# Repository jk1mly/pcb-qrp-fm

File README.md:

# pcb-qrp-fm
おもちゃのトランシーバ用のICを使うための基板

ハムフェア2023でPRUGブースに置いたもの
フィルタ（特に145M）は改善の余地あり

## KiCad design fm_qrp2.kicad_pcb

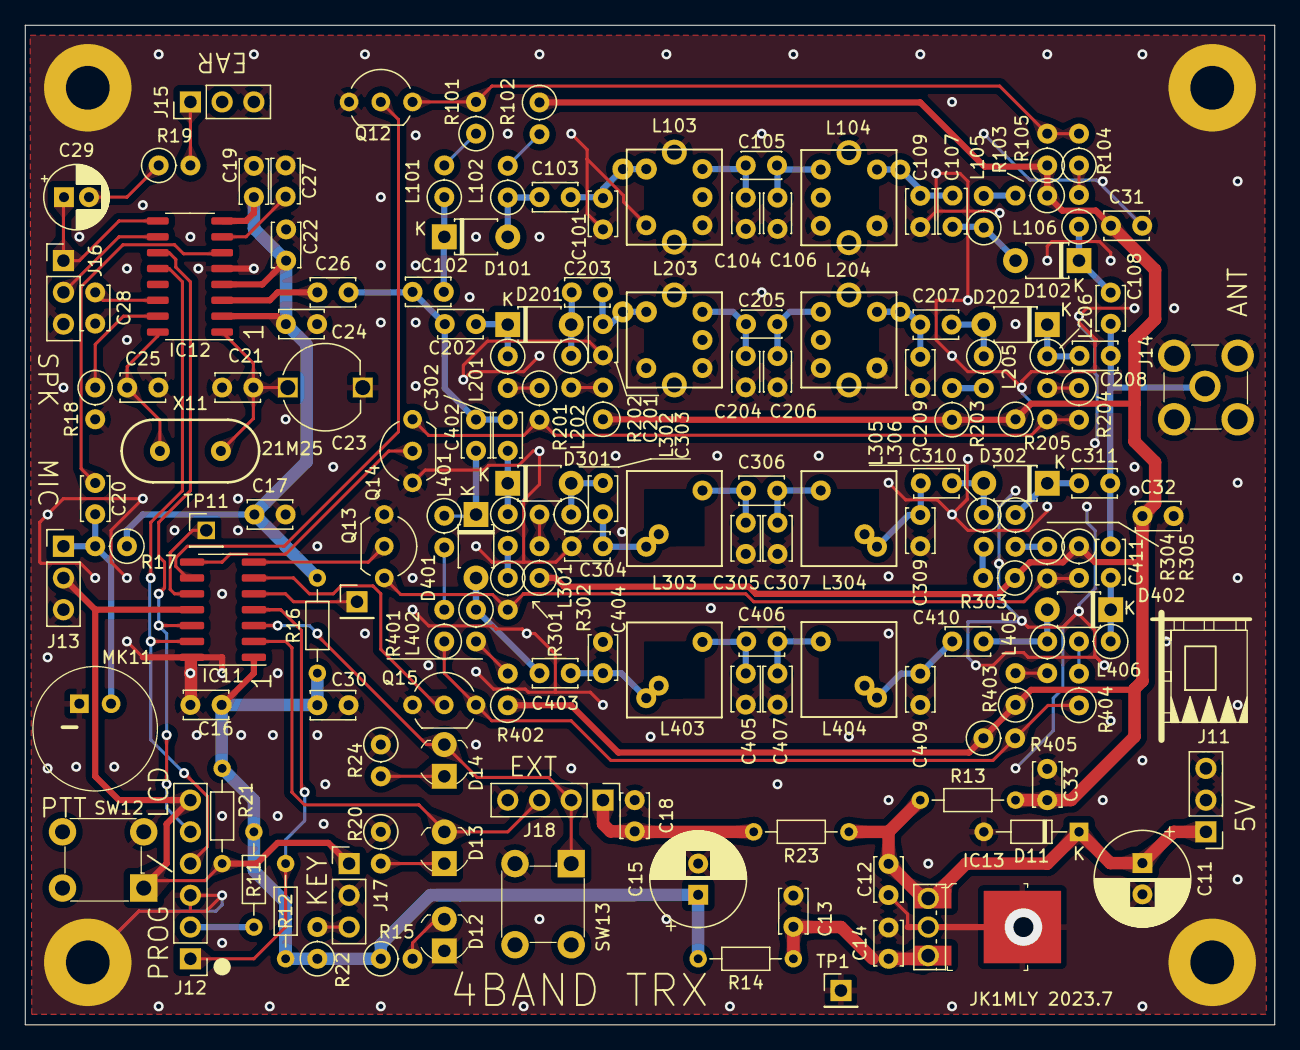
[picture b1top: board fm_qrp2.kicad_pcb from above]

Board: 2 copper layers, 100.0 x 80.0 mm, 156 parts (0 on the bottom side), 90 nets.

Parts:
C11, C15: 470u; CP_Radial_D7.5mm_P2.50mm
C12, C13, C14, C16, C18, C20, C30, C31, C32: 0.1u; C_Disc_D3.4mm_W2.1mm_P2.50mm
C17, C19, C22, C24, C27, C28, C33: 1u; C_Disc_D3.4mm_W2.1mm_P2.50mm
C21, C407: 22p; C_Disc_D3.4mm_W2.1mm_P2.50mm
C23: 10p; C_TRIM_P6.00mm
C25: 27p; C_Disc_D3.4mm_W2.1mm_P2.50mm
C26: 0.01u; C_Disc_D3.4mm_W2.1mm_P2.50mm
C29: 10u; CP_Radial_D5.0mm_P2.00mm
C101, C109, C201, C209, C405: NM; C_Disc_D3.4mm_W2.1mm_P2.50mm
C102, C108: 4700p; C_Disc_D3.4mm_W2.1mm_P2.50mm
C103, C107, C202, C203, C207, C208: 2200p; C_Disc_D3.4mm_W2.1mm_P2.50mm
C104, C106: 33p; C_Disc_D3.0mm_W2.0mm_P2.50mm
C105: 6p; C_Disc_D3.0mm_W2.0mm_P2.50mm
C204, C206: 15p; C_Disc_D3.0mm_W2.0mm_P2.50mm
C205: 2p; C_Disc_D3.0mm_W2.0mm_P2.50mm
C302, C303, C310, C311, C402, C403, C410, C411: 1000p; C_Disc_D3.4mm_W2.1mm_P2.50mm
C304, C305, C307, C309: 15p; C_Disc_D3.4mm_W2.1mm_P2.50mm
C306: 33p; C_Disc_D3.4mm_W2.1mm_P2.50mm
C404, C409: 10p; C_Disc_D3.4mm_W2.1mm_P2.50mm
C406: 4p; C_Disc_D3.4mm_W2.1mm_P2.50mm
D11: 1N4007; D_DO-34_SOD68_P7.62mm_Horizontal
D12, D13, D14: LED; LED_3mm_Radial
D101, D102, D201, D202, D301, D302, D401, D402: 1SS277; D_T-1_P5.08mm_Horizontal
IC11: PIC16F1503T-I/SL; SO-14_3.9x8.65mm_P1.27mm
IC12: BK4802P; SO-16_3.9x9.9mm_P1.27mm
IC13: LM2940T-3.3; TO-251-3_Vertical
J11, J13, J15, J16, J17: Conn_01x03; PinHeader_1x03_P2.54mm_Vertical
J12: Conn_01x06; PinHeader_1x06_P2.54mm_Vertical
J14: Conn_Coaxial; RF_SMA_Vertical_5-1814832-1
J18: Conn_01x04; PinHeader_1x04_P2.54mm_Vertical
L101, L102, L105, L106, L201, L202, L205, L206, L301, L302, L305, L306, L401, L402, L405, L406: 1u; R_Axial_DIN0207_L6.3mm_D2.5mm_P2.54mm_Vertical
L103, L104: 7S25; coil_7mm
L203, L204: 7S50; coil_7mm
L303, L304, L403, L404: 50n; coil3_7mm
MK11: Microphone; Mic_CMA-4544PF-W
Q12, Q13, Q14, Q15: 2N7000; TO-92_Inline_Wide
R11, R13, R14, R16: 0; R_Axial_DIN0204_L3.6mm_D1.6mm_P7.62mm_Horizontal
R12: 1k; R_Axial_DIN0204_L3.6mm_D1.6mm_P7.62mm_Horizontal
R15, R17, R20, R24, R101, R102, R103, R104, R105, R201, R202, R203, R204, R205, R301, R302, R303, R304, R305, R401, R402, R403, R404, R405: 1k; R_Axial_DIN0207_L6.3mm_D2.5mm_P2.54mm_Vertical
R18: 4.7k; R_Axial_DIN0207_L6.3mm_D2.5mm_P2.54mm_Vertical
R19, R22: 10; R_Axial_DIN0207_L6.3mm_D2.5mm_P2.54mm_Vertical
R21: 10k; R_Axial_DIN0204_L3.6mm_D1.6mm_P7.62mm_Horizontal
R23: 10; R_Axial_DIN0204_L3.6mm_D1.6mm_P7.62mm_Horizontal
SW12, SW13: SW_Push; Switch_Tactile_THT_6x6mm
TP1, TP11, TP12: TestPoint; PinHeader_1x01_P2.54mm_Vertical
TP2, TP3, TP4, TP5: M3; MountingHole_3.5mm_Pad
U12: NJM2391DL1-33; TO-252-3
X11: 21.25M; HC49

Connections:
+3V3: C15.1, C16.2, C30.1, IC11.1 (VDD), R11.2, R12.1, R14.2, R15.1, R16.1, R21.1, R22.1
+5V: C31.1, C32.1, C33.1, R13.2, R102.1, R103.1, R105.1, R202.1, R203.1, R205.1, R302.1, R303.1, R305.1, R402.1, R403.1, R405.1
/RF-IC/+3.3V-REG: C13.1, C14.1, IC13.3 (VO), R14.1, U12.3 (VO)
/RF-IC/+3.3V-TR: C17.1, C19.2, C22.2, C24.2, IC12.2 (VCCRF), IC12.4 (VCCPA), IC12.8 (VCCAUD), R16.2, R17.1
/RF-IC/+5VIN: C11.1, C12.1, D11.1 (K), IC13.1 (VI), J11.1, R13.1, R23.1, U12.1 (VI)
B28: Q12.3 (D), R101.2, R104.2, R105.2
B50: Q14.3 (D), R201.2, R204.2, R205.2
B144: Q13.3 (D), R301.2, R304.2, R305.2
B430: Q15.3 (D), R401.1, R404.1, R405.2
GND: C11.2, C12.2, C13.2, C14.2, C15.2, C16.1, C17.2, C18.2, C19.1, C21.2, C22.1, C23.2, C24.1, C25.2, C27.2, C28.2, C30.2, C31.2, C32.2, C33.2, C101.2, C104.2, C106.2, C109.2, C201.2, C204.2, C206.2, C209.2, C304.2, C305.2, C307.1, C309.2, C404.2, C405.2, C407.1, C409.2, D11.2 (A), D12.1 (K), IC11.14 (VSS), IC12.5 (VSS), IC13.2 (GND), J11.2, J11.3, J12.3, J13.3, J14.1 (G), J15.3, J16.3, J17.2, J18.4, L103.1 (PR1), L103.5 (S2), L103.6 (G1), L103.7 (G2), L104.3 (PR2), L104.4 (S1), L104.6 (G1), L104.7 (G2), L203.1 (PR1), L203.5 (S2), L203.6 (G1), L203.7 (G2), L204.3 (PR2), L204.4 (S1), L204.6 (G1), L204.7 (G2), MK11.1 (-), Q12.1 (S), Q13.1 (S), Q14.1 (S), Q15.1 (S), R18.2, R20.1, R24.1, SW12.2, SW13.2, TP1.1, TP2.1, TP3.1, TP4.1, TP5.1, U12.2 (GND)
unnamed: C29.2, R19.1
unnamed: C303.2, C304.1, L303.1
unnamed: C305.1, C306.1, L303.2
unnamed: C306.2, C307.2, L304.1
unnamed: C309.1, C310.1, L304.2
unnamed: C403.2, C404.1, L403.1
unnamed: C405.1, C406.1, L403.2
unnamed: C406.2, C407.2, L404.1
unnamed: C409.1, C410.1, L404.2
unnamed: D12.2 (A), R15.2
unnamed: D13.2 (A), IC11.2 (RA5/T1CKI/NCO1CLK/CLCIN1/CLKIN), J18.3
unnamed: D13.1 (K), R20.2
unnamed: D14.2 (A), IC11.3 (RA4/AN3/T1G/NCO1/SDO/CLKOUT), J18.2, SW13.1
unnamed: D14.1 (K), R24.2
unnamed: C103.1, D101.2 (A), L102.1
unnamed: C102.2, D101.1 (K), L101.1
unnamed: C107.2, D102.2 (A), L105.1
unnamed: C108.1, D102.1 (K), L106.1
unnamed: C203.1, D201.2 (A), L202.1
unnamed: C202.2, D201.1 (K), L201.1
unnamed: C207.2, D202.2 (A), L205.1
unnamed: C208.1, D202.1 (K), L206.1
unnamed: C303.1, D301.2 (A), L302.1
unnamed: C302.2, D301.1 (K), L301.1
unnamed: C310.2, D302.2 (A), L305.1
unnamed: C311.1, D302.1 (K), L306.1
unnamed: C403.1, D401.2 (A), L402.1
unnamed: C402.2, D401.1 (K), L401.1
unnamed: C410.2, D402.2 (A), L405.1
unnamed: C411.1, D402.1 (K), L406.1
unnamed: IC11.6 (CLC2IN1/CWG1B/C2OUT/RC4), Q15.2 (G)
unnamed: IC11.5 (PWM1/CLC1/CWG1A/RC5), TP12.1
unnamed: IC11.13 (RA0/AN0/DACOUT1/C1IN+/ICSPDAT), IC12.12 (SDATA), J12.4
unnamed: IC11.12 (RA1/AN1/Vref+/C1IN0-/C2IN0-/ICSPCLK), IC12.11 (SCK), J12.5
unnamed: IC11.11 (RA2/AN2/DACOUT2/C1OUT/T0CKI/~CWG1FLT/CL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), J12.6, J13.2, J17.1, R21.2, SW12.1
unnamed: IC11.4 (RA3/T1G/CLC1IN0/~SS/~MCLR/Vpp), J12.1, R12.2
unnamed: IC11.10 (SCK/SCL/CLC2/C2IN+/AN4/RC0), TP11.1
unnamed: IC11.9 (SDI/SDA/PWM4/NCO1/C2IN1-/C1IN1-/AN5/RC1), Q12.2 (G)
unnamed: IC11.8 (SDO/C2IN2-/C1IN2-/AN6/RC2), Q14.2 (G)
unnamed: IC11.7 (~SS/PWM2/CLCIN0/C2IN3-/C1IN3-/AN7/RC3), Q13.2 (G)
unnamed: C26.1, IC12.3 (ANT)
unnamed: C27.1, IC12.7 (AUDC)
unnamed: C28.1, IC12.14 (CDVDD)
unnamed: IC12.10 (EARON), J16.2
unnamed: C29.1, IC12.9 (EAROP), J16.1
unnamed: C20.2, IC12.6 (MIC)
unnamed: IC12.15 (SQ), R18.1
unnamed: C21.1, C23.1, IC12.1 (XI), X11.1
unnamed: C25.1, IC12.16 (XO), X11.2
unnamed: J12.2, R11.1
unnamed: C20.1, J13.1, MK11.2 (+), R17.2
unnamed: J15.1, R19.2
unnamed: J17.3, R22.2
unnamed: C18.1, J18.1, R23.2
unnamed: L101.2, R101.1
unnamed: L102.2, R102.2
unnamed: C104.1, C105.2, L103.3 (PR2)
unnamed: C101.1, C103.2, L103.4 (S1)
unnamed: C105.1, C106.1, L104.1 (PR1)
unnamed: C107.1, C109.1, L104.5 (S2)
unnamed: L105.2, R103.2
unnamed: L106.2, R104.1
unnamed: L201.2, R201.1
unnamed: L202.2, R202.2
unnamed: C204.1, C205.2, L203.3 (PR2)
unnamed: C201.1, C203.2, L203.4 (S1)
unnamed: C205.1, C206.1, L204.1 (PR1)
unnamed: C207.1, C209.1, L204.5 (S2)
unnamed: L205.2, R203.2
unnamed: L206.2, R204.1
unnamed: L301.2, R301.1
unnamed: L302.2, R302.2
unnamed: L305.2, R303.2
unnamed: L306.2, R304.1
unnamed: L401.2, R401.2
unnamed: L402.2, R402.2
unnamed: L405.2, R403.2
unnamed: L406.2, R404.2
RFANT: C108.2, C208.2, C311.2, C411.2, J14.2 (S)
RFIO: C26.2, C102.1, C202.1, C302.1, C402.1

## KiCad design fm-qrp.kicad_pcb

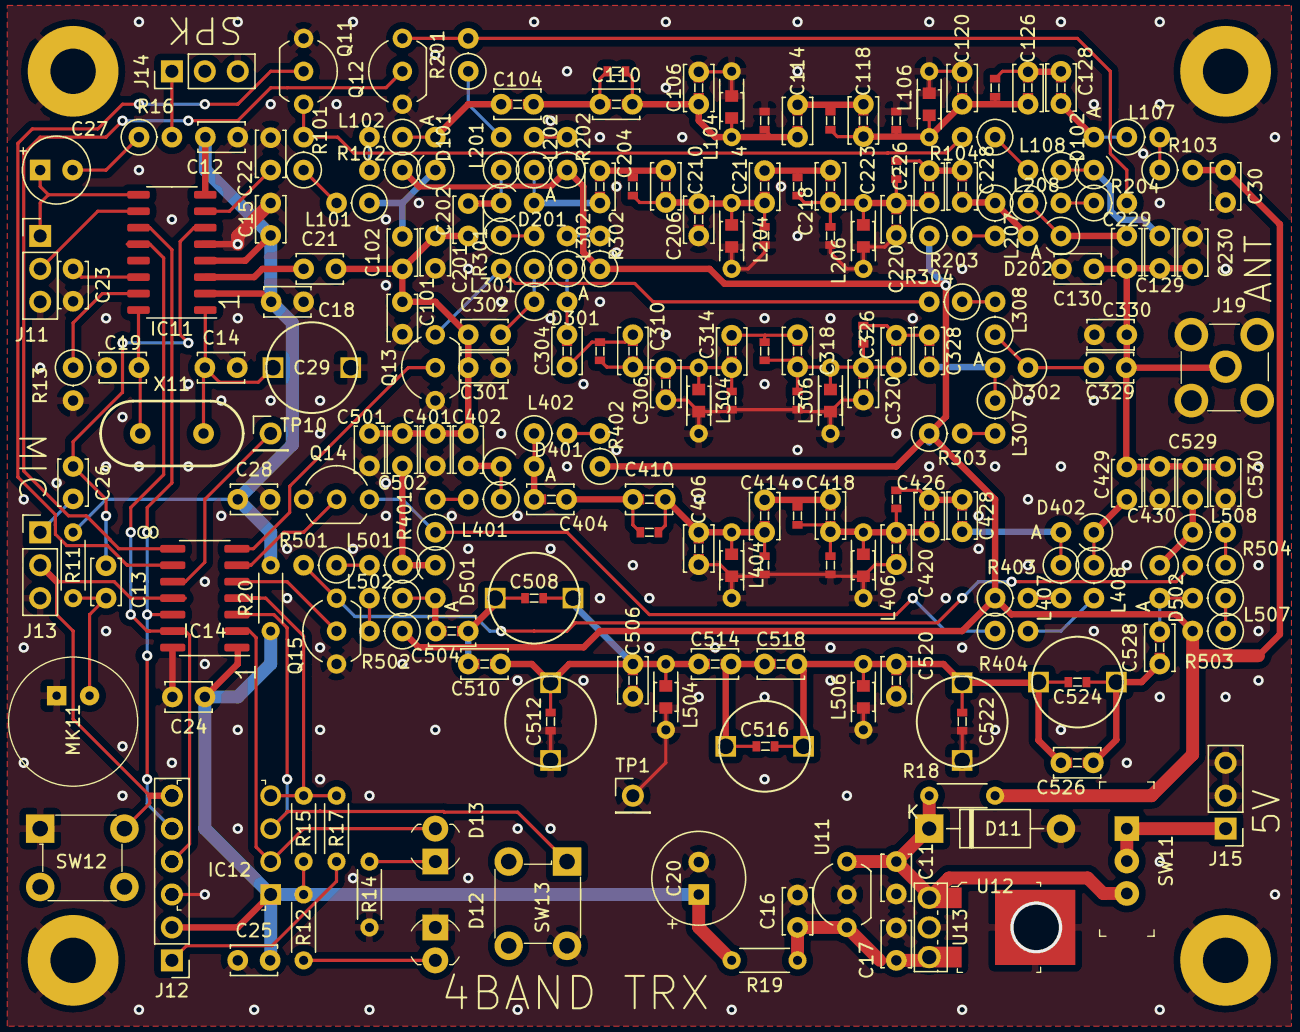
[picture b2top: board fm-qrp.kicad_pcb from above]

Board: 2 copper layers, 261 parts (0 on the bottom side), 107 nets.

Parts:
C11, C13, C16, C17, C24, C25, C26, C30: 0.1u; C_Disc_D3.4mm_W2.1mm_P2.50mm
C12, C15, C18, C22, C23, C28: 1u; C_Disc_D3.4mm_W2.1mm_P2.50mm
C14, C19: 15p; C_Disc_D3.4mm_W2.1mm_P2.50mm
C20: 10u; CP_Radial_Tantal_D7.0mm_P2.50mm
C21: 100p; C_Disc_D3.4mm_W2.1mm_P2.50mm
C27: 10u; CP_Radial_Tantal_D5.0mm_P2.50mm
C29, C508, C512, C516, C522, C524: 10p; C_TRIM_P6.00mm
C101, C102, C104, C106, C110, C114, C118, C120, C126, C128, C129, C130, C201, C202, C204, C206, C210, C214, C218, C220, C226, C228, C229, C230, C301, C302, C304, C306, C310, C314, C318, C320, C326, C328, C329, C330, C401, C402, C404, C406, C410, C414, C418, C420, C426, C428, C429, C430, C501, C502, C504, C506, C510, C514, C518, C520, C526, C528, C529, C530: 10p; C_Disc_D3.4mm_W2.1mm_P2.50mm
C103, C105, C107, C109, C111, C113, C115, C117, C119, C121, C123, C125, C127, C203, C205, C207, C209, C211, C213, C215, C217, C219, C221, C223, C225, C227, C303, C305, C307, C309, C311, C313, C315, C317, C319, C321, C323, C325, C327, C403, C405, C407, C409, C411, C413, C415, C417, C419, C421, C423, C425, C427, C503, C505, C507, C509, C511, C513, C515, C517, C519, C521, C523, C525, C527: 1p; 0603
D11: 1N4002; D_DO-41_SOD81_P10.16mm_Horizontal
D12, D13: LED; LED_3mm_Radial
D101, D102, D201, D202, D301, D302, D401, D402, D501, D502: 1SS277; D_A-405_P2.54mm_Vertical_AnodeUp
IC11: BK4802P; SO-16_3.9x9.9mm_P1.27mm
IC12: PIC12LF1501-IP; DIP-8_W7.62mm
IC14: PIC16F1503-ISL; SO-14_3.9x8.65mm_P1.27mm
J11, J13, J14, J15: Conn_01x03; PinHeader_1x03_P2.54mm_Vertical
J12: Conn_01x06; PinHeader_1x06_P2.54mm_Vertical
J19: Conn_Coaxial; RF_SMA_Vertical_5-1814832-1
L101, L102, L107, L108, L201, L202, L207, L208, L301, L302, L307, L308, L401, L402, L407, L408, L501, L502, L507, L508: 1u; R_Axial_DIN0207_L6.3mm_D2.5mm_P2.54mm_Vertical
L103, L105, L203, L205, L303, L305, L403, L405, L503, L505: 10n; L_Murata_LQH2MCNxxxx02_2.0x1.6mm
L104, L106, L204, L206, L304, L306, L404, L406, L504, L506: 1u; R_Axial_DIN0204_L3.6mm_D1.6mm_P5.08mm_Horizontal
MK11: Microphone; Mic_CMA-4544PF-W
Q11, Q12, Q13, Q14, Q15: 2N7000; TO-92_Inline_Wide
R11, R12, R14, R15: 1k; R_Axial_DIN0204_L3.6mm_D1.6mm_P5.08mm_Horizontal
R13, R16, R101, R102, R103, R104, R201, R202, R203, R204, R301, R302, R303, R304, R401, R402, R403, R404, R501, R502, R503, R504: 1k; R_Axial_DIN0207_L6.3mm_D2.5mm_P2.54mm_Vertical
R17, R18, R19, R20: 0; R_Axial_DIN0204_L3.6mm_D1.6mm_P5.08mm_Horizontal
SW11: SW_SPDT; Switch_Slide_11.6x4mm_EG1218
SW12, SW13: SW_Push; Switch_Tactile_THT_6x6mm
TP1, TP10: TestPoint; PinHeader_1x01_P2.54mm_Vertical
TP2, TP3, TP4, TP5: M3; MountingHole_3.5mm_Pad
U11: LM2936-3.0_TO92; TO-92_Inline_Wide
U12: LM2936-3.0; TO-252-3
U13: LM2936-3.0; TO-251-3_Vertical
X11: Crystal; HC49

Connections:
+3V3: C20.1, C24.1, C25.2, IC12.1, IC14.1, J12.2, R12.1, R15.1, R19.2, R20.1
+5V: C30.1, R18.2, R102.1, R103.2, R202.1, R203.1, R302.1, R303.1, R402.1, R403.1, R502.1, R503.2
/RF-IC/+3.3V-REG: C16.1, C17.1, R19.1, U11.1, U12.3, U13.3
/RF-IC/+3.3V-TR: C12.2, C15.2, C18.2, C28.1, IC11.2, IC11.4, IC11.8, R11.1, R20.2
/RF-IC/+5VIN: C11.1, D11.1, R18.1, SW11.3, U11.3, U12.1, U13.1
B28: Q11.3, R101.2, R104.2
B50: Q12.3, R201.2, R204.2
B144: Q13.3, R301.2, R304.2
B430: Q14.3, R401.1, R404.1
BTUN: Q15.3, R501.2, R504.2
GND: C11.2, C12.1, C14.2, C15.1, C16.2, C17.2, C18.1, C19.2, C20.2, C22.2, C23.2, C24.2, C25.1, C28.2, C29.2, C30.2, C101.2, C105.2, C106.2, C111.2, C119.2, C120.2, C121.2, C130.2, C201.2, C205.2, C206.2, C211.2, C219.2, C220.2, C221.2, C230.2, C301.2, C305.2, C306.2, C311.2, C319.2, C320.2, C321.2, C330.2, C401.2, C405.2, C406.2, C411.2, C419.2, C420.2, C421.2, C430.2, C501.2, C505.2, C506.2, C511.2, C512.2, C519.2, C520.2, C521.2, C522.2, C530.2, D11.2, D12.1, IC11.5, IC12.8, IC14.14, J11.3, J12.3, J13.3, J14.3, J15.2, J15.3, J19.1, L103.2, L104.2, L105.2, L106.2, L203.2, L204.2, L205.2, L206.2, L303.2, L304.2, L305.2, L306.2, L403.2, L404.2, L405.2, L406.2, L503.2, L504.2, L505.2, L506.2, MK11.1, Q11.1, Q12.1, Q13.1, Q14.1, Q15.1, R13.2, R14.2, SW12.1, SW13.2, TP1.1, TP2.1, TP3.1, TP4.1, TP5.1, U11.2, U12.2, U13.2
unnamed: C13.1, MK11.2, R11.2
unnamed: C13.2, C26.1, IC11.6
unnamed: C14.1, C29.1, IC11.1, X11.1
unnamed: C19.1, IC11.16, X11.2
unnamed: C21.1, IC11.3
unnamed: C22.1, IC11.7
unnamed: C23.1, IC11.14
unnamed: C26.2, J13.1
unnamed: C27.1, IC11.9, J11.1
unnamed: C27.2, R16.1
unnamed: C102.2, D101.1, L101.1
unnamed: C103.1, C104.1, D101.2, L102.1
unnamed: C103.2, C104.2, C107.1, C109.1, C110.1
unnamed: C105.1, C106.1, C107.2, C109.2, C110.2, C111.1, C113.1, C114.1, L103.1, L104.1
unnamed: C113.2, C114.2, C115.1, C117.1, C118.1
unnamed: C115.2, C117.2, C118.2, C119.1, C120.1, C121.1, C123.1, C125.1, C126.1, L105.1, L106.1
unnamed: C123.2, C125.2, C126.2, C127.1, C128.1
unnamed: C127.2, C128.2, D102.2, L107.1
unnamed: C129.1, D102.1, L108.1
unnamed: C202.2, D201.1, L201.1
unnamed: C203.1, C204.1, D201.2, L202.1
unnamed: C203.2, C204.2, C207.1, C209.1, C210.1
unnamed: C205.1, C206.1, C207.2, C209.2, C210.2, C211.1, C213.1, C214.1, L203.1, L204.1
unnamed: C213.2, C214.2, C215.1, C217.1, C218.1
unnamed: C215.2, C217.2, C218.2, C219.1, C220.1, C221.1, C223.1, C225.1, C226.1, L205.1, L206.1
unnamed: C223.2, C225.2, C226.2, C227.1, C228.1
unnamed: C227.2, C228.2, D202.2, L207.1
unnamed: C229.1, D202.1, L208.1
unnamed: C302.2, D301.1, L301.1
unnamed: C303.1, C304.1, D301.2, L302.1
unnamed: C303.2, C304.2, C307.1, C309.1, C310.1
unnamed: C305.1, C306.1, C307.2, C309.2, C310.2, C311.1, C313.1, C314.1, L303.1, L304.1
unnamed: C313.2, C314.2, C315.1, C317.1, C318.1
unnamed: C315.2, C317.2, C318.2, C319.1, C320.1, C321.1, C323.1, C325.1, C326.1, L305.1, L306.1
unnamed: C323.2, C325.2, C326.2, C327.1, C328.1
unnamed: C327.2, C328.2, D302.2, L307.1
unnamed: C329.1, D302.1, L308.1
unnamed: C402.2, D401.1, L401.1
unnamed: C403.1, C404.1, D401.2, L402.1
unnamed: C403.2, C404.2, C407.1, C409.1, C410.1
unnamed: C405.1, C406.1, C407.2, C409.2, C410.2, C411.1, C413.1, C414.1, L403.1, L404.1
unnamed: C413.2, C414.2, C415.1, C417.1, C418.1
unnamed: C415.2, C417.2, C418.2, C419.1, C420.1, C421.1, C423.1, C425.1, C426.1, L405.1, L406.1
unnamed: C423.2, C425.2, C426.2, C427.1, C428.1
unnamed: C427.2, C428.2, D402.2, L407.1
unnamed: C429.1, D402.1, L408.1
unnamed: C502.2, D501.1, L501.1
unnamed: C503.1, C504.1, D501.2, L502.1
unnamed: C503.2, C504.2, C507.1, C508.2, C509.1, C510.1
unnamed: C505.1, C506.1, C507.2, C508.1, C509.2, C510.2, C511.1, C512.1, C513.1, C514.1, L503.1, L504.1
unnamed: C513.2, C514.2, C515.1, C516.2, C517.1, C518.1
unnamed: C515.2, C516.1, C517.2, C518.2, C519.1, C520.1, C521.1, C522.1, C523.1, C524.2, C525.1, C526.1, L505.1, L506.1
unnamed: C523.2, C524.1, C525.2, C526.2, C527.1, C528.1
unnamed: C527.2, C528.2, D502.2, L507.2
unnamed: C529.1, D502.1, L508.1
unnamed: D12.2, R12.2
unnamed: D13.1, R14.1
unnamed: D13.2, IC12.2, IC14.2
unnamed: IC11.10, J11.2
unnamed: IC11.11, IC12.6, IC14.12, J12.5
unnamed: IC11.12, IC12.7, IC14.13, J12.4
unnamed: IC11.15, R13.1
unnamed: IC12.3, IC14.3, SW13.1
unnamed: IC12.4, IC14.4, R15.2, R17.2
unnamed: IC12.5, IC14.11, J12.6, J13.2, SW12.2
unnamed: IC14.5, Q15.2
unnamed: IC14.6, Q14.2
unnamed: IC14.7, Q13.2
unnamed: IC14.8, Q12.2
unnamed: IC14.9, Q11.2
unnamed: IC14.10, TP10.1
unnamed: J12.1, R17.1
unnamed: J14.1, R16.2
unnamed: J15.1, SW11.1, SW11.2
unnamed: L101.2, R101.1
unnamed: L102.2, R102.2
unnamed: L107.2, R103.1
unnamed: L108.2, R104.1
unnamed: L201.2, R201.1
unnamed: L202.2, R202.2
unnamed: L207.2, R203.2
unnamed: L208.2, R204.1
unnamed: L301.2, R301.1
unnamed: L302.2, R302.2
unnamed: L307.2, R303.2
unnamed: L308.2, R304.1
unnamed: L401.2, R401.2
unnamed: L402.2, R402.2
unnamed: L407.2, R403.2
unnamed: L408.2, R404.2
unnamed: L501.2, R501.1
unnamed: L502.2, R502.2
unnamed: L507.1, R503.1
unnamed: L508.2, R504.1
RFANT: C129.2, C130.1, C229.2, C230.1, C329.2, C330.1, C429.2, C430.1, C529.2, C530.1, J19.2
RFIO: C21.2, C101.1, C102.1, C201.1, C202.1, C301.1, C302.1, C401.1, C402.1, C501.1, C502.1

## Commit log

2022-03-08 trial
2022-03-08 jumper
    タクトスイッチの配線ミス
    スイッチのリードをカットして実装 IMG_5911.jpegでcutの位置
    ジャンパ配線 IMG_5911.jpegの2本
2022-03-12 部品定数を入力 ただし未評価
2022-03-12 部品実装用
2022-03-12 シルク表示修正
2022-03-21 バンドパスフィルタの定数を見直し（単体試験の反映）
2023-06-25 Add files via upload
    フィルタ回路変更とジャンパクリーン
2023-07-17 assembly
2023-08-06 モノバンド版
2023-08-06 アップデート
2023-08-06 製作の説明 ドラフト版
